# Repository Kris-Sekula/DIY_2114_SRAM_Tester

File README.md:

This repository contans a modified version of PCB for the 2114 SRAM chip, the original desing was published [here](https://github.com/gpimblott/SRAM2114_Tester) 

My version makes it much easier to manufacture the PCB at home (DYI method with toner transfer)

Finished product:

This is how the PCB looks like when home made:

I published a [YouTube](https://youtu.be/o5B_jiQg0Gk) video that details the work.

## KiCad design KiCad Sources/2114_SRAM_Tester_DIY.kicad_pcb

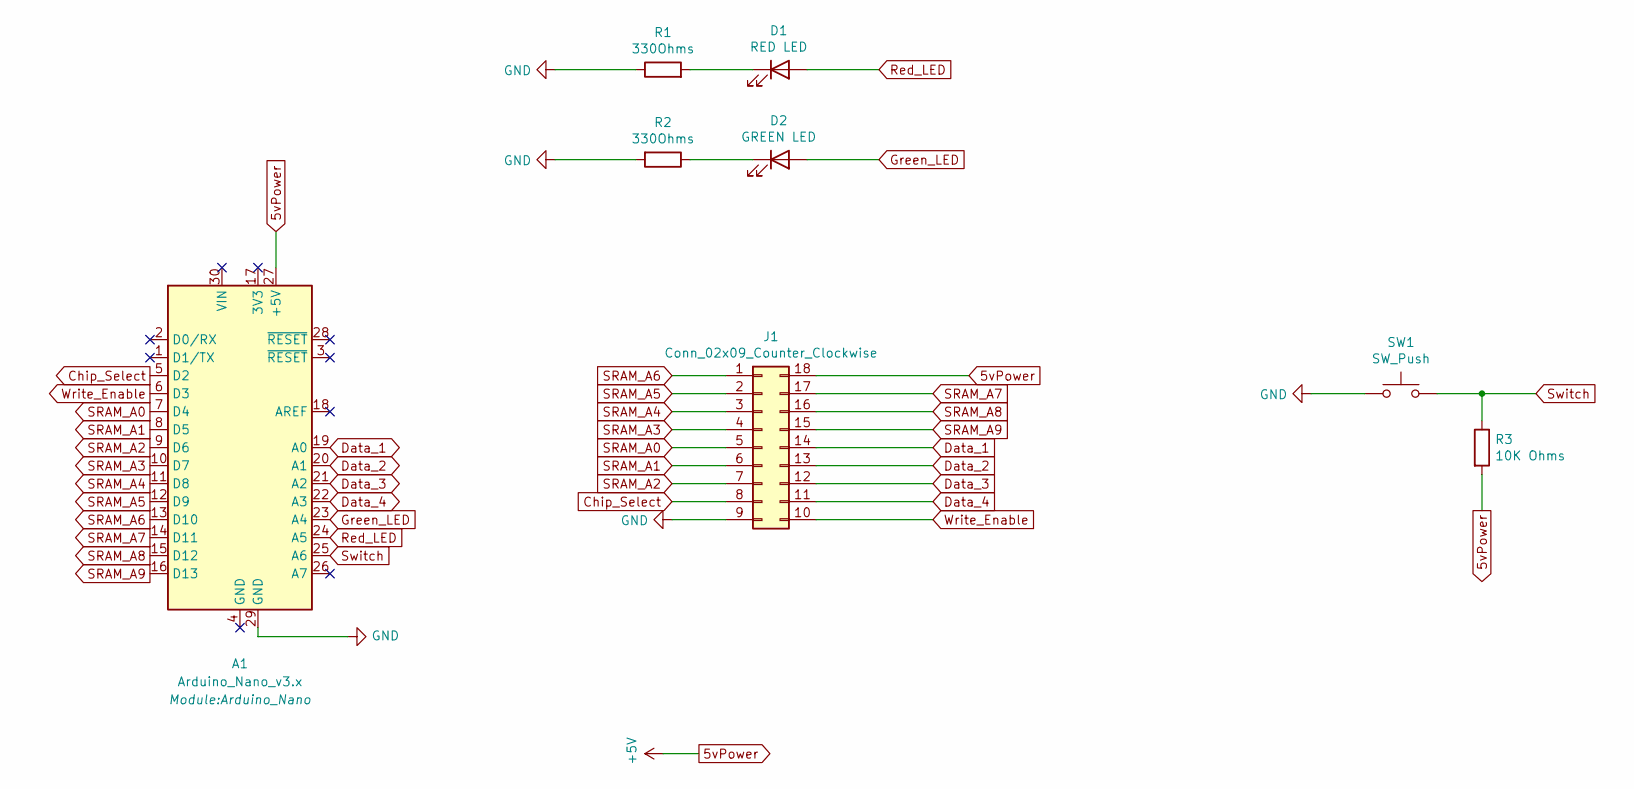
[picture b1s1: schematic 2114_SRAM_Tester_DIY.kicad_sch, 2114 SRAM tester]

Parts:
A1: Arduino_Nano_v3.x; Arduino_Nano
D1: RED LED; LED_D4.0mm
D2: GREEN LED; LED_D4.0mm
J1: Conn_02x09_Counter_Clockwise; DIP-18_W7.62mm_Socket
R1, R2: 330Ohms; R_Axial_DIN0309_L9.0mm_D3.2mm_P12.70mm_Horizontal
R3: 10K Ohms; R_Axial_DIN0309_L9.0mm_D3.2mm_P12.70mm_Horizontal
SW1: SW_Push; SW_PUSH_6mm

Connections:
5vPower: A1.27 (+5V), J1.18, R3.2
Chip_Select: A1.5 (D2), J1.8
Data_1: A1.19 (A0), J1.14
Data_2: A1.20 (A1), J1.13
Data_3: A1.21 (A2), J1.12
Data_4: A1.22 (A3), J1.11
GND: A1.29 (GND), J1.9, R1.1, R2.2, SW1.1
Green_LED: A1.23 (A4), D2.2 (A)
unnamed: D1.1 (K), R1.2
unnamed: D2.1 (K), R2.1
Red_LED: A1.24 (A5), D1.2 (A)
SRAM_A0: A1.7 (D4), J1.5
SRAM_A1: A1.8 (D5), J1.6
SRAM_A2: A1.9 (D6), J1.7
SRAM_A3: A1.10 (D7), J1.4
SRAM_A4: A1.11 (D8), J1.3
SRAM_A5: A1.12 (D9), J1.2
SRAM_A6: A1.13 (D10), J1.1
SRAM_A7: A1.14 (D11), J1.17
SRAM_A8: A1.15 (D12), J1.16
SRAM_A9: A1.16 (D13), J1.15
Switch: A1.25 (A6), R3.1, SW1.2
Write_Enable: A1.6 (D3), J1.10

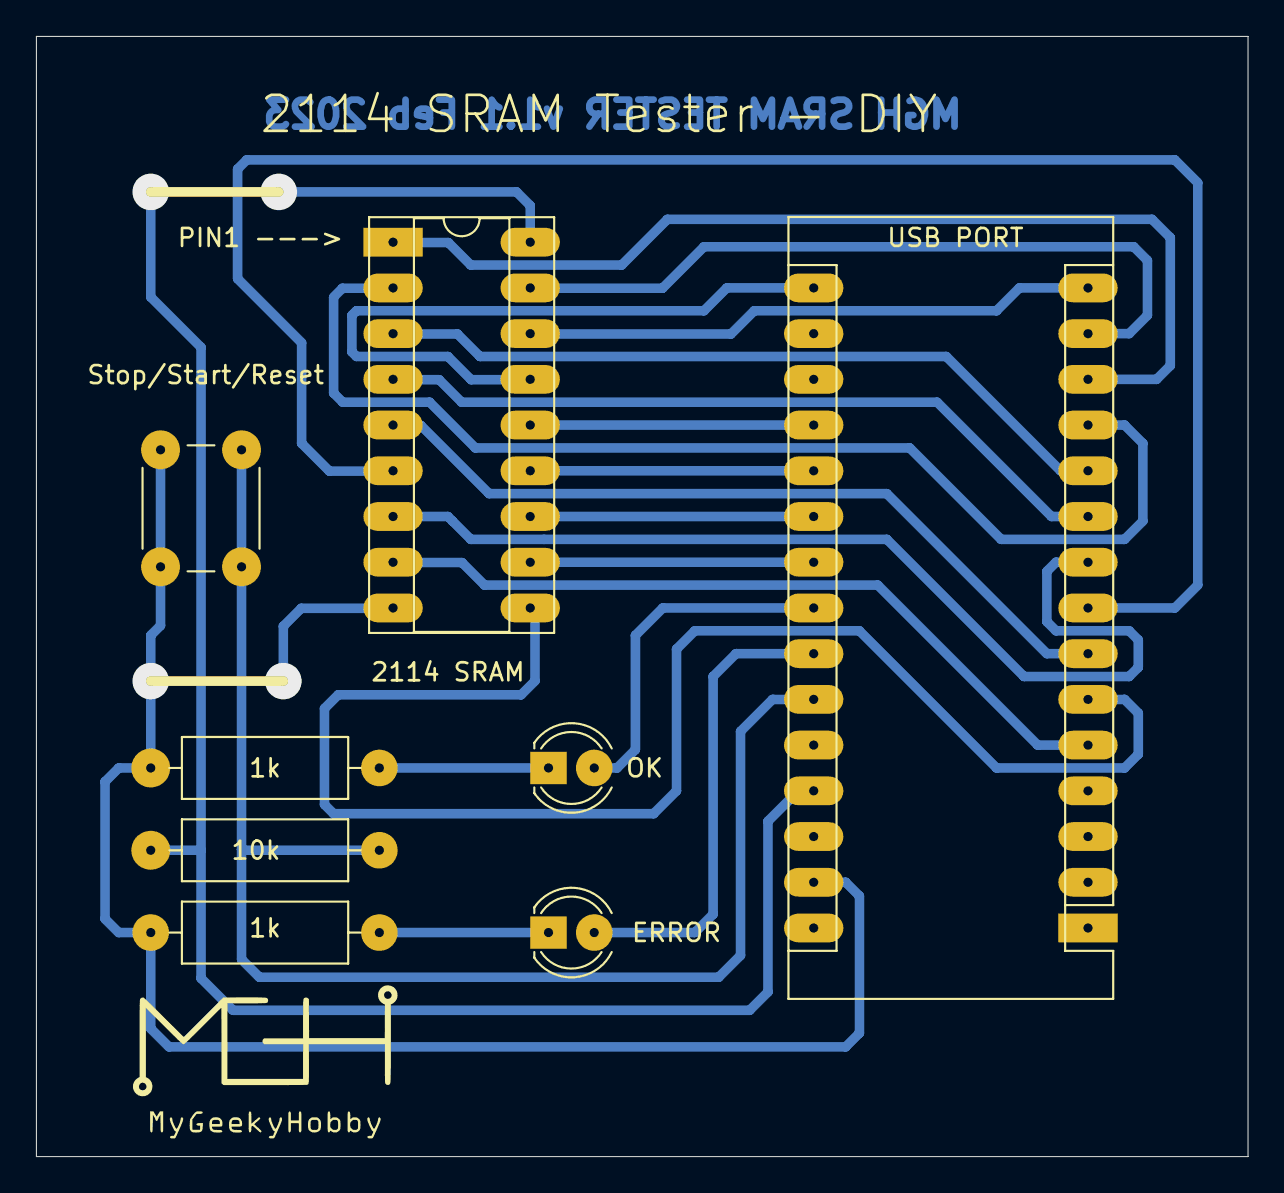
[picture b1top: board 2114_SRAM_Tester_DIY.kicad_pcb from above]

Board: 2 copper layers, 67.3 x 62.2 mm, 8 parts (0 on the bottom side), 23 nets.

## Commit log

2023-02-20 Added YouTube video.
